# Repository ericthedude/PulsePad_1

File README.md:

PulsePad

A custom macropad using a Seeed XIAO RP2040

Features

-4 reprogrammable keys

-Reprogrammable Rotary Encoder

-OLED display

-Media control layer

-Arrow key layer

Layer 0 (Media control layer)
              
                 MUTE          Rotary Encoder (Turn for volume, click to change layers)

Prev. Track    Play/Pause    Next Track        

Layer 1 (Arrow key layer)
            
              Up Arrow       Rotary Encoder (Turn for scrolling, click to change layers)

Left Arrow   Down Arrow   Right Arrow        

Hardware

-Seeed XIAO RP2040

-EC11 Rotary Encoder

-128x32 OLED

OLED States

Layer 0: Media

Layer 1: Arrows

[bom.csv](https://github.com/user-attachments/files/34785335/bom.csv)
name,price
Seeed Xiao RP2040,7
PCB,8
Heat Set Inserts,2
M2 Screws,1
M2 Heat Set Inserts,1
Total,19

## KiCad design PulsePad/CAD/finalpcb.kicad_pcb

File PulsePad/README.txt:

**I will finish the firmware once I recieve the parts**

PulsePad
A custom macropad using a Seeed XIAO RP2040

Features
-4 reprogrammable keys
-Reprogrammable Rotary Encoder
-OLED display
-Media control layer
-Arrow key layer

Layer 0 (Media control layer)
                 MUTE          Rotary Encoder (Turn for volume, click to change layers)
Prev. Track    Play/Pause    Next Track        

Layer 1 (Arrow key layer)
              Up Arrow       Rotary Encoder (Turn for scrolling, click to change layers)
Left Arrow   Down Arrow   Right Arrow        

Hardware
-Seeed XIAO RP2040
-EC11 Rotary Encoder
-128x32 OLED

OLED States
Layer 0: Media
Layer 1: Arrows

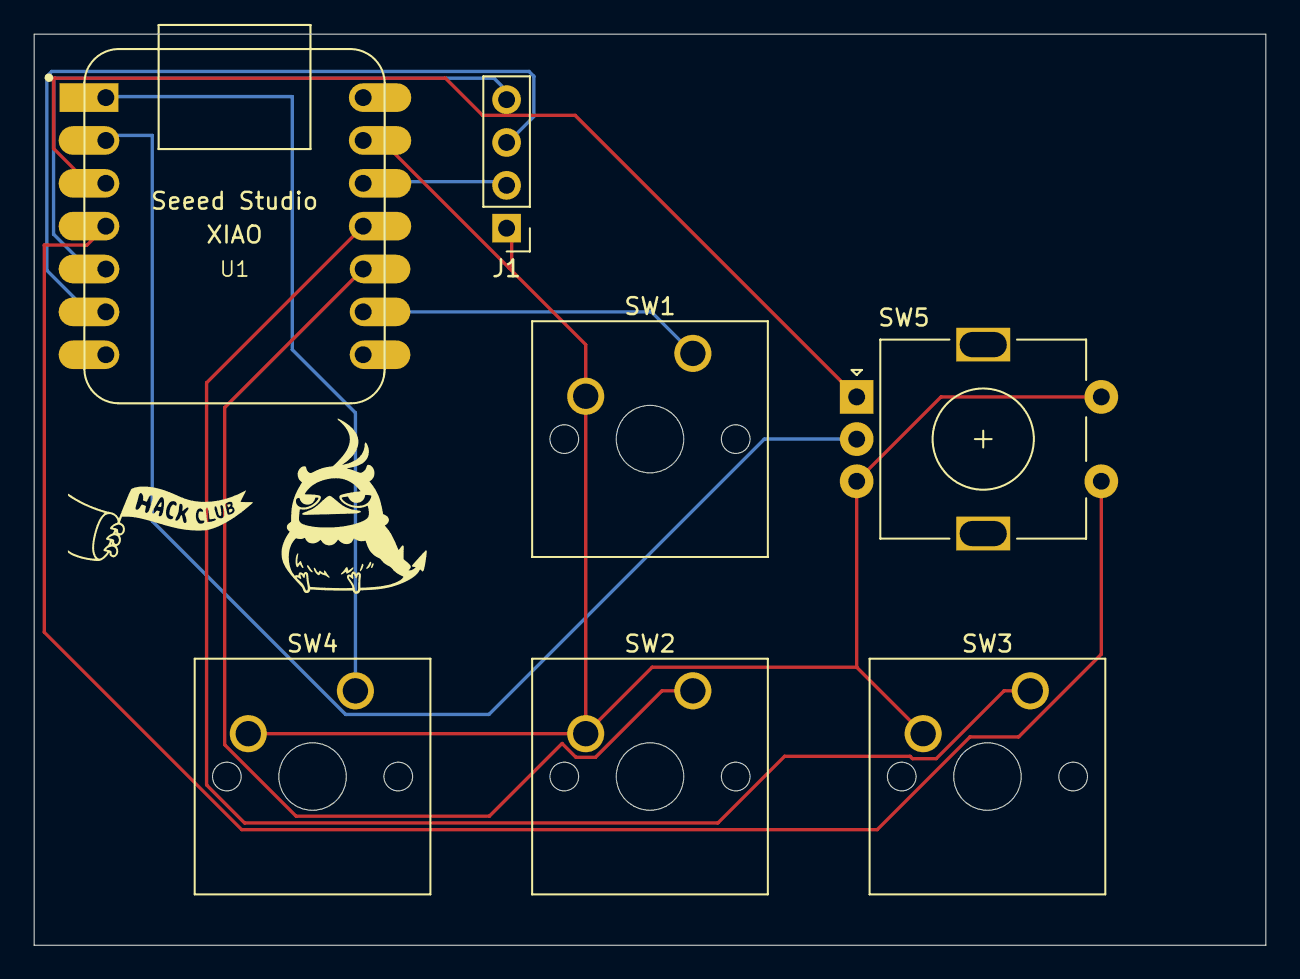
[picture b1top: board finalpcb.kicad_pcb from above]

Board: 2 copper layers, 73.0 x 54.0 mm, 7 parts (0 on the bottom side), 11 nets.

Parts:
J1: Conn_01x04_Pin; PinHeader_1x04_P2.54mm_Vertical
SW1: SW_Push_45deg; SW_Cherry_MX_1.00u_PCB
SW2, SW3, SW4: SW_Push_45deg; SW_Cherry_MX_1.50u_PCB
SW5: RotaryEncoder_Switch; RotaryEncoder_Alps_EC11E-Switch_Vertical_H20mm
U1: MOUDLE-SEEEDUINO-XIAO; XIAO-Generic-Hybrid-14P-2.54-21X17.8MM

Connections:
GND: J1.GND (Pin_1_1), SW1.2, SW2.2, SW3.2, SW4.2, SW5.B, SW5.S2, U1.13 (GND)
unnamed: J1.J1 (Pin_4_4), U1.5 (PA8_A4_D4_SDA)
unnamed: J1.J2 (Pin_3_3), U1.6 (PA9_A5_D5_SCL)
unnamed: J1.J3 (Pin_2_2), U1.12 (3V3)
unnamed: SW4.1, U1.1 (PA02_A0_D0)
unnamed: SW5.C, U1.2 (PA4_A1_D1)
unnamed: SW2.1, U1.10 (PA5_A9_D9_MISO)
unnamed: SW3.1, U1.11 (PA6_A10_D10_MOSI)
unnamed: SW1.1, U1.9 (PA7_A8_D8_SCK)
unnamed: SW5.A, U1.3 (PA10_A2_D2)
unnamed: SW5.S1, U1.4 (PA11_A3_D3)
